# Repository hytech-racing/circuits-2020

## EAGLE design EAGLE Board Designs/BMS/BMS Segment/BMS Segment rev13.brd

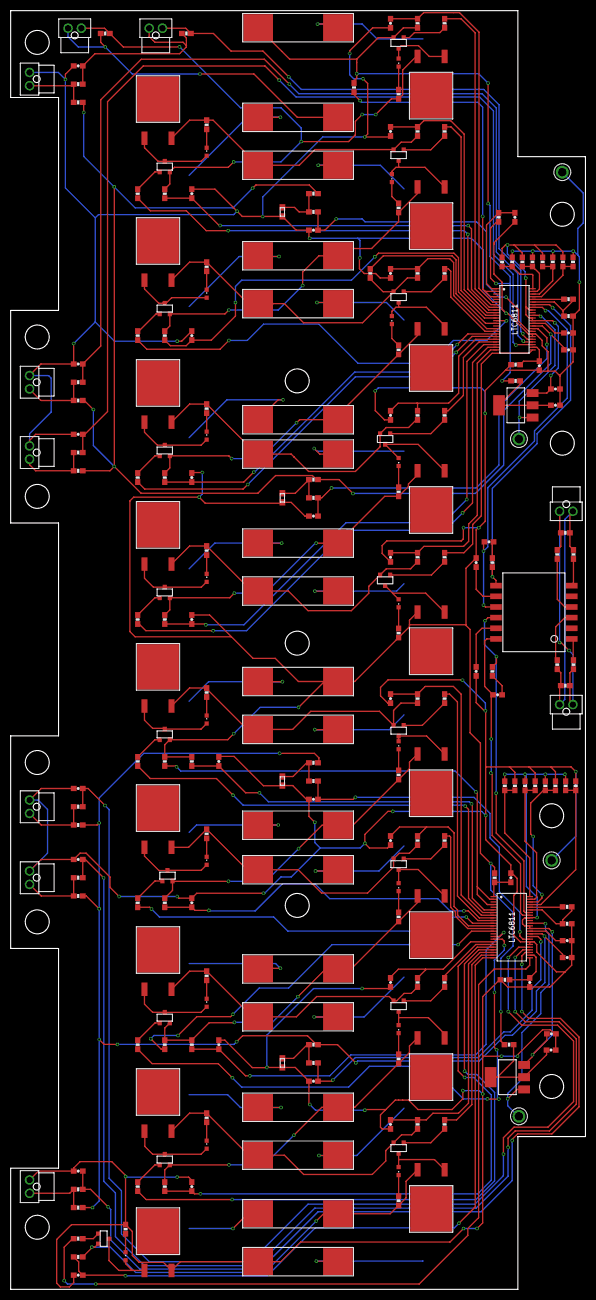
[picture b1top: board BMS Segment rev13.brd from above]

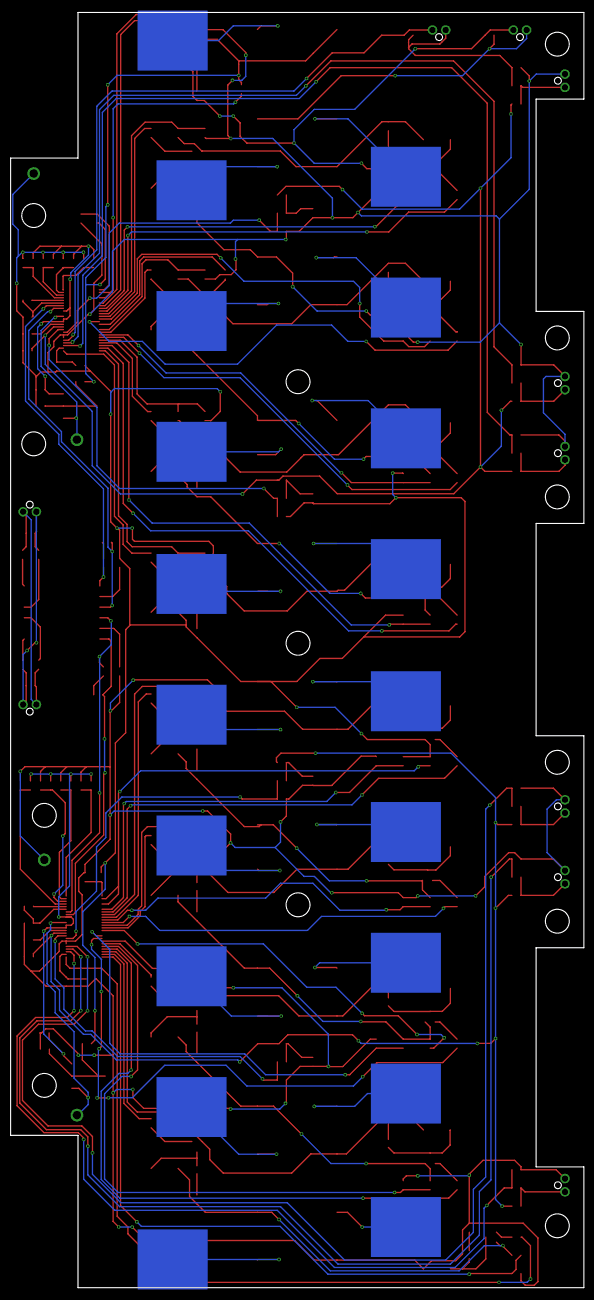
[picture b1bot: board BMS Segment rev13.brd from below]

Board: 2 copper layers, 108.0 x 240.3 mm, 286 parts (19 on the bottom side), 194 nets.

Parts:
AMS_CELL_TEST: AMS_CELL_TEST; NANO-FIT_VERTICAL-2
AMS_THERM_TEST: AMS_THERM_TEST; NANO-FIT_VERTICAL-2
C1_A, C1_B, C2_A, C2_B, C8_A, C8_B: 1uF; 0603-CAP
C3_A, C3_B: 15pF; 0603-CAP
C4_A, C4_B, C5_A: 10nF; 0603-CAP
C6_A, C6_B, C7_A, C7_B: 100nF; 0603-CAP
CELL0, CELL1, CELL2, CELL3, CELL4, CELL5, CELL6, CELL7, CELL8, CELL9, CELL10, CELL11, CELL12, CELL13, CELL14, CELL15, CELL16, CELL17, CELL18: BATTERY_SPRING_KEYSTONE5222; KEYSTONE5222
C_5: 10nF; 0603-CAP
DRAIN1:C, DRAIN2:C, DRAIN3:C, DRAIN4:C, DRAIN5:C, DRAIN6:C, DRAIN7:C, DRAIN8:C, DRAIN9:C, DRAIN10:C, DRAIN11:C, DRAIN12:C, DRAIN13:C, DRAIN14:C, DRAIN15:C, DRAIN16:C, DRAIN17:C, DRAIN18:C: 10nF; 0603-CAP
DRAIN1:DISCHARGE, DRAIN2:DISCHARGE, DRAIN3:DISCHARGE, DRAIN4:DISCHARGE, DRAIN5:DISCHARGE, DRAIN6:DISCHARGE, DRAIN7:DISCHARGE, DRAIN8:DISCHARGE, DRAIN9:DISCHARGE, DRAIN10:DISCHARGE, DRAIN11:DISCHARGE, DRAIN12:DISCHARGE, DRAIN13:DISCHARGE, DRAIN14:DISCHARGE, DRAIN15:DISCHARGE, DRAIN16:DISCHARGE, DRAIN17:DISCHARGE, DRAIN18:DISCHARGE: 5R; PWR163
DRAIN1:GATE, DRAIN2:GATE, DRAIN3:GATE, DRAIN4:GATE, DRAIN5:GATE, DRAIN6:GATE, DRAIN7:GATE, DRAIN8:GATE, DRAIN9:GATE, DRAIN10:GATE, DRAIN11:GATE, DRAIN12:GATE, DRAIN13:GATE, DRAIN14:GATE, DRAIN15:GATE, DRAIN16:GATE, DRAIN17:GATE, DRAIN18:GATE: 3K3; 0603-RES
DRAIN1:LED1, DRAIN2:LED1, DRAIN3:LED1, DRAIN4:LED1, DRAIN5:LED1, DRAIN6:LED1, DRAIN7:LED1, DRAIN8:LED1, DRAIN9:LED1, DRAIN10:LED1, DRAIN11:LED1, DRAIN12:LED1, DRAIN13:LED1, DRAIN14:LED1, DRAIN15:LED1, DRAIN16:LED1, DRAIN17:LED1, DRAIN18:LED1: RED; LED-603
DRAIN1:PFET, DRAIN2:PFET, DRAIN3:PFET, DRAIN4:PFET, DRAIN5:PFET, DRAIN6:PFET, DRAIN7:PFET, DRAIN8:PFET, DRAIN9:PFET, DRAIN10:PFET, DRAIN11:PFET, DRAIN12:PFET, DRAIN13:PFET, DRAIN14:PFET, DRAIN15:PFET, DRAIN16:PFET, DRAIN17:PFET, DRAIN18:PFET: P-CHANNEL_MOSFET_DMP3099L-7; SOT23
DRAIN1:R, DRAIN2:R, DRAIN3:R, DRAIN4:R, DRAIN5:R, DRAIN6:R, DRAIN7:R, DRAIN8:R, DRAIN9:R, DRAIN10:R, DRAIN11:R, DRAIN12:R, DRAIN13:R, DRAIN14:R, DRAIN15:R, DRAIN16:R, DRAIN17:R, DRAIN18:R: 100R; 0603-RES
DRAIN1:R1, DRAIN2:R1, DRAIN3:R1, DRAIN4:R1, DRAIN5:R1, DRAIN6:R1, DRAIN7:R1, DRAIN8:R1, DRAIN9:R1, DRAIN10:R1, DRAIN11:R1, DRAIN12:R1, DRAIN13:R1, DRAIN14:R1, DRAIN15:R1, DRAIN16:R1, DRAIN17:R1, DRAIN18:R1: 806R; 0603-RES
F0, F1, F2, F3, F4, F5, F6, F7, F8, F9, F10, F11, F12, F13, F14, F15, F16, F17, F18: 0001.2704.11; 5X20MM_FUSE
ISOSPI_A: ISOSPI; NANO-FIT_VERTICAL-2
ISOSPI_B: ISOSPI; NANO-FIT_VERTICAL-2
J1_A, J1_B, J2_A, J2_B, J3_A, J3_B, J4_A, J4_B, J5_A, J5_B, J6_A, J6_B, J7_A, J7_B, J8_A, J8_B: 0R; 0603-RES
J_CELL_A: 0R; 0603-RES
J_THERM_A: 0R; 0603-RES
Q1, Q2: NSV1C201MZ4; SOT223
R1_A, R1_B, R2_A, R2_B: 100R; 0603-RES
R3_A, R3_B: 402R; 0603-RES
R4_A, R4_B, R5_A, R5_B: 22R; 0603-RES
RB1_A, RB1_B: 1K2; 0603-RES
RB2_A, RB2_B: 806R; 0603-RES
RIN_A: 100R; 0603-RES
RIN_B: 100R; 0603-RES
RM_A: 100R; 0603-RES
RM_B: 100R; 0603-RES
RU1_A, RU1_B, RU2_A, RU2_B: 100R; 0603-RES
THERM1, THERM2, THERM3, THERM4: 10K; 0603
THERM1_A, THERM1_B, THERM2_A, THERM2_B, THERM3_A, THERM3_B: THERMISTOR; NANO-FIT_VERTICAL-2
THERM_FILTER1:C, THERM_FILTER2:C, THERM_FILTER3:C, THERM_FILTER4:C, THERM_FILTER5:C, THERM_FILTER6:C, THERM_FILTER7:C, THERM_FILTER8:C, THERM_FILTER9:C, THERM_FILTER10:C: 10nF; 0603-CAP
THERM_FILTER1:R, THERM_FILTER2:R, THERM_FILTER3:R, THERM_FILTER4:R, THERM_FILTER5:R, THERM_FILTER6:R, THERM_FILTER7:R, THERM_FILTER8:R, THERM_FILTER9:R, THERM_FILTER10:R: 100R; 0603-RES
THERM_FILTER1:R1, THERM_FILTER2:R1, THERM_FILTER3:R1, THERM_FILTER4:R1, THERM_FILTER5:R1, THERM_FILTER6:R1, THERM_FILTER7:R1, THERM_FILTER8:R1, THERM_FILTER9:R1, THERM_FILTER10:R1: 10K; 0603-RES
TRANSFORMER: HM2102NLT
U1, U2: LTC6811-2; LTC6811
U$5, U$6, U$7, U$8: TEST_POINT
U$9, U$10, U$11, U$12, U$13, U$14, U$15, U$16, U$17, U$18, U$19, U$26, U$27: M4_MOUNTING

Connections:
C0_A: C5_A.1, R2_A.2, U1.26
C0_B: C_5.1, R2_B.2, U2.26
C1_A: DRAIN10:C.1, DRAIN10:R.2, U1.24
C1_B: DRAIN1:C.1, DRAIN1:R.2, U2.24
C2_A: DRAIN11:C.1, DRAIN11:R.2, U1.22
C2_B: DRAIN2:C.1, DRAIN2:R.2, U2.22
C3_A: DRAIN12:C.1, DRAIN12:R.2, U1.20
C3_B: DRAIN3:C.1, DRAIN3:R.2, U2.20
C4_A: DRAIN13:C.1, DRAIN13:R.2, U1.18
C4_B: DRAIN4:C.1, DRAIN4:R.2, U2.18
C5_A: DRAIN14:C.1, DRAIN14:R.2, U1.16
C5_B: DRAIN5:C.1, DRAIN5:R.2, U2.16
C7_A: DRAIN15:C.1, DRAIN15:R.2, U1.12
C7_B: DRAIN6:C.1, DRAIN6:R.2, U2.12
C8_A: DRAIN16:C.1, DRAIN16:R.2, U1.10
C8_B: DRAIN7:C.1, DRAIN7:R.2, U2.10
C9_A: DRAIN17:C.1, DRAIN17:R.2, U1.8
C9_B: DRAIN8:C.1, DRAIN8:R.2, U2.8
C10_A: DRAIN18:C.1, DRAIN18:R.2, U1.6
C10_B: DRAIN9:C.1, DRAIN9:R.2, U2.6
CC0: CELL0.P$1, F0.P$1
CC1: CELL1.P$1, F1.P$1
CC2: CELL2.P$1, F2.P$1
CC3: CELL3.P$1, F3.P$1
CC4: CELL4.P$1, F4.P$1
CC5: CELL5.P$1, F5.P$1
CC6: CELL6.P$1, F6.P$1
CC7: CELL7.P$1, F7.P$1
CC8: CELL8.P$1, F8.P$1
CC9: CELL9.P$1, F9.P$1
CC10: CELL10.P$1, F10.P$1
CC11: CELL11.P$1, F11.P$1
CC12: CELL12.P$1, F12.P$1
CC13: CELL13.P$1, F13.P$1
CC14: CELL14.P$1, F14.P$1
CC15: CELL15.P$1, F15.P$1
CC16: CELL16.P$1, F16.P$1
CC17: CELL17.P$1, F17.P$1
CC18: CELL18.P$1, F18.P$1
DRAIN1:GATE: DRAIN1:GATE.1, DRAIN1:PFET.1
DRAIN1:N$1: DRAIN1:DISCHARGE.1, DRAIN1:LED1.A, DRAIN1:PFET.3
DRAIN1:N$2: DRAIN1:LED1.C, DRAIN1:R1.2
DRAIN2:GATE: DRAIN2:GATE.1, DRAIN2:PFET.1
DRAIN2:N$1: DRAIN2:DISCHARGE.1, DRAIN2:LED1.A, DRAIN2:PFET.3
DRAIN2:N$2: DRAIN2:LED1.C, DRAIN2:R1.2
DRAIN3:GATE: DRAIN3:GATE.1, DRAIN3:PFET.1
DRAIN3:N$1: DRAIN3:DISCHARGE.1, DRAIN3:LED1.A, DRAIN3:PFET.3
DRAIN3:N$2: DRAIN3:LED1.C, DRAIN3:R1.2
DRAIN4:GATE: DRAIN4:GATE.1, DRAIN4:PFET.1
DRAIN4:N$1: DRAIN4:DISCHARGE.1, DRAIN4:LED1.A, DRAIN4:PFET.3
DRAIN4:N$2: DRAIN4:LED1.C, DRAIN4:R1.2
DRAIN5:GATE: DRAIN5:GATE.1, DRAIN5:PFET.1
DRAIN5:N$1: DRAIN5:DISCHARGE.1, DRAIN5:LED1.A, DRAIN5:PFET.3
DRAIN5:N$2: DRAIN5:LED1.C, DRAIN5:R1.2
DRAIN6:GATE: DRAIN6:GATE.1, DRAIN6:PFET.1
DRAIN6:N$1: DRAIN6:DISCHARGE.1, DRAIN6:LED1.A, DRAIN6:PFET.3
DRAIN6:N$2: DRAIN6:LED1.C, DRAIN6:R1.2
DRAIN7:GATE: DRAIN7:GATE.1, DRAIN7:PFET.1
DRAIN7:N$1: DRAIN7:DISCHARGE.1, DRAIN7:LED1.A, DRAIN7:PFET.3
DRAIN7:N$2: DRAIN7:LED1.C, DRAIN7:R1.2
DRAIN8:GATE: DRAIN8:GATE.1, DRAIN8:PFET.1
DRAIN8:N$1: DRAIN8:DISCHARGE.1, DRAIN8:LED1.A, DRAIN8:PFET.3
DRAIN8:N$2: DRAIN8:LED1.C, DRAIN8:R1.2
DRAIN9:GATE: DRAIN9:GATE.1, DRAIN9:PFET.1
DRAIN9:N$1: DRAIN9:DISCHARGE.1, DRAIN9:LED1.A, DRAIN9:PFET.3
DRAIN9:N$2: DRAIN9:LED1.C, DRAIN9:R1.2
DRAIN10:GATE: DRAIN10:GATE.1, DRAIN10:PFET.1
DRAIN10:N$1: DRAIN10:DISCHARGE.1, DRAIN10:LED1.A, DRAIN10:PFET.3
DRAIN10:N$2: DRAIN10:LED1.C, DRAIN10:R1.2
DRAIN11:GATE: DRAIN11:GATE.1, DRAIN11:PFET.1
DRAIN11:N$1: DRAIN11:DISCHARGE.1, DRAIN11:LED1.A, DRAIN11:PFET.3
DRAIN11:N$2: DRAIN11:LED1.C, DRAIN11:R1.2
DRAIN12:GATE: DRAIN12:GATE.1, DRAIN12:PFET.1
DRAIN12:N$1: DRAIN12:DISCHARGE.1, DRAIN12:LED1.A, DRAIN12:PFET.3
DRAIN12:N$2: DRAIN12:LED1.C, DRAIN12:R1.2
DRAIN13:GATE: DRAIN13:GATE.1, DRAIN13:PFET.1
DRAIN13:N$1: DRAIN13:DISCHARGE.1, DRAIN13:LED1.A, DRAIN13:PFET.3
DRAIN13:N$2: DRAIN13:LED1.C, DRAIN13:R1.2
DRAIN14:GATE: DRAIN14:GATE.1, DRAIN14:PFET.1
DRAIN14:N$1: DRAIN14:DISCHARGE.1, DRAIN14:LED1.A, DRAIN14:PFET.3
DRAIN14:N$2: DRAIN14:LED1.C, DRAIN14:R1.2
DRAIN15:GATE: DRAIN15:GATE.1, DRAIN15:PFET.1
DRAIN15:N$1: DRAIN15:DISCHARGE.1, DRAIN15:LED1.A, DRAIN15:PFET.3
DRAIN15:N$2: DRAIN15:LED1.C, DRAIN15:R1.2
DRAIN16:GATE: DRAIN16:GATE.1, DRAIN16:PFET.1
DRAIN16:N$1: DRAIN16:DISCHARGE.1, DRAIN16:LED1.A, DRAIN16:PFET.3
DRAIN16:N$2: DRAIN16:LED1.C, DRAIN16:R1.2
DRAIN17:GATE: DRAIN17:GATE.1, DRAIN17:PFET.1
DRAIN17:N$1: DRAIN17:DISCHARGE.1, DRAIN17:LED1.A, DRAIN17:PFET.3
DRAIN17:N$2: DRAIN17:LED1.C, DRAIN17:R1.2
DRAIN18:GATE: DRAIN18:GATE.1, DRAIN18:PFET.1
DRAIN18:N$1: DRAIN18:DISCHARGE.1, DRAIN18:LED1.A, DRAIN18:PFET.3
DRAIN18:N$2: DRAIN18:LED1.C, DRAIN18:R1.2
DRIVE_A: Q1.1, U1.38, U$8.P$1
DRIVE_B: Q2.1, U2.38, U$7.P$1
GPIO1_A: THERM_FILTER6:C.1, THERM_FILTER6:R.1, U1.27
GPIO1_B: THERM_FILTER1:C.1, THERM_FILTER1:R.1, U2.27
GPIO2_A: THERM_FILTER7:C.1, THERM_FILTER7:R.1, U1.28
GPIO2_B: THERM_FILTER2:C.1, THERM_FILTER2:R.1, U2.28
GPIO3_A_POST: AMS_THERM_TEST.P$2, J_THERM_A.1, U1.29
GPIO3_A_PRE: AMS_THERM_TEST.P$1, J_THERM_A.2, THERM_FILTER8:C.1, THERM_FILTER8:R.1
GPIO3_B: THERM_FILTER3:C.1, THERM_FILTER3:R.1, U2.29
GPIO4_A: THERM_FILTER9:C.1, THERM_FILTER9:R.1, U1.32
GPIO4_B: THERM_FILTER4:C.1, THERM_FILTER4:R.1, U2.32
GPIO5_A: THERM_FILTER10:C.1, THERM_FILTER10:R.1, U1.33
GPIO5_B: THERM_FILTER5:C.1, THERM_FILTER5:R.1, U2.33
IM_A: C3_A.2, TRANSFORMER.P$9, U1.41
IM_B: C3_B.2, TRANSFORMER.P$12, U2.41
IP_A: R3_A.1, TRANSFORMER.P$7, U1.42
IP_B: R3_B.1, TRANSFORMER.P$10, U2.42
ISOSPI-M: ISOSPI_A.P$2, ISOSPI_B.P$2, R5_A.2, R5_B.2, RM_A.2, RM_B.2
ISOSPI-P: ISOSPI_A.P$1, ISOSPI_B.P$1, R4_A.2, R4_B.2, RM_A.1, RM_B.1
unnamed: C4_B.1, TRANSFORMER.P$11
unnamed: RB1_B.2, U2.44
unnamed: THERM1_B.P$1, THERM_FILTER1:R.2, THERM_FILTER1:R1.2
unnamed: RB1_B.1, RB2_B.2, U2.43
unnamed: R4_B.1, TRANSFORMER.P$3
unnamed: RB1_A.2, U1.44
unnamed: R5_B.1, TRANSFORMER.P$1
unnamed: J7_B.1, J8_B.1, U2.48
unnamed: J5_B.1, J6_B.1, U2.47
unnamed: C3_B.1, R3_B.2
unnamed: J3_B.1, J4_B.1, U2.46
unnamed: J1_B.1, J2_B.1, U2.45
unnamed: THERM1.2, THERM_FILTER5:R.2, THERM_FILTER5:R1.2
unnamed: THERM2_B.P$1, THERM_FILTER2:R.2, THERM_FILTER2:R1.2
unnamed: THERM2.2, THERM_FILTER4:R.2, THERM_FILTER4:R1.2
unnamed: RB1_A.1, RB2_A.2, U1.43
unnamed: C4_A.1, TRANSFORMER.P$8
unnamed: R4_A.1, TRANSFORMER.P$6
unnamed: R5_A.1, TRANSFORMER.P$4
unnamed: C3_A.1, R3_A.2
unnamed: THERM3_B.P$1, THERM_FILTER3:R.2, THERM_FILTER3:R1.2
unnamed: J7_A.1, J8_A.1, U1.48
unnamed: J5_A.1, J6_A.1, U1.47
unnamed: J3_A.1, J4_A.1, U1.46
unnamed: J1_A.1, J2_A.1, U1.45
unnamed: THERM4.2, THERM_FILTER9:R.2, THERM_FILTER9:R1.2
unnamed: THERM3_A.P$1, THERM_FILTER8:R.2, THERM_FILTER8:R1.2
unnamed: THERM3.2, THERM_FILTER10:R.2, THERM_FILTER10:R1.2
unnamed: THERM2_A.P$1, THERM_FILTER7:R.2, THERM_FILTER7:R1.2
unnamed: THERM1_A.P$1, THERM_FILTER6:R.2, THERM_FILTER6:R1.2
S1_A: DRAIN10:GATE.2, U1.25
S1_B: DRAIN1:GATE.2, U2.25
S2_A: DRAIN11:GATE.2, U1.23
S2_B: DRAIN2:GATE.2, U2.23
S3_A: DRAIN12:GATE.2, U1.21
S3_B: DRAIN3:GATE.2, U2.21
S4_A: DRAIN13:GATE.2, U1.19
S4_B: DRAIN4:GATE.2, U2.19
S5_A: DRAIN14:GATE.2, U1.17
S5_B: DRAIN5:GATE.2, U2.17
S7_A: DRAIN15:GATE.2, U1.13
S7_B: DRAIN6:GATE.2, U2.13
S8_A: DRAIN16:GATE.2, U1.11
S8_B: DRAIN7:GATE.2, U2.11
S9_A: DRAIN17:GATE.2, U1.9
S9_B: DRAIN8:GATE.2, U2.9
S10_A: DRAIN18:GATE.2, U1.7
S10_B: DRAIN9:GATE.2, U2.7
SENSE1: DRAIN1:PFET.2, DRAIN1:R.1, DRAIN2:DISCHARGE.2, DRAIN2:R1.1, F1.P$2
SENSE2: DRAIN2:PFET.2, DRAIN2:R.1, DRAIN3:DISCHARGE.2, DRAIN3:R1.1, F2.P$2
SENSE3: DRAIN3:PFET.2, DRAIN3:R.1, DRAIN4:DISCHARGE.2, DRAIN4:R1.1, F3.P$2
SENSE4: DRAIN4:PFET.2, DRAIN4:R.1, DRAIN5:DISCHARGE.2, DRAIN5:R1.1, F4.P$2
SENSE5: DRAIN5:PFET.2, DRAIN5:R.1, DRAIN6:DISCHARGE.2, DRAIN6:R1.1, F5.P$2, RU2_B.1
SENSE6: DRAIN6:PFET.2, DRAIN6:R.1, DRAIN7:DISCHARGE.2, DRAIN7:R1.1, F6.P$2
SENSE7: DRAIN7:PFET.2, DRAIN7:R.1, DRAIN8:DISCHARGE.2, DRAIN8:R1.1, F7.P$2
SENSE8: DRAIN8:PFET.2, DRAIN8:R.1, DRAIN9:DISCHARGE.2, DRAIN9:R1.1, F8.P$2
SENSE10: DRAIN10:PFET.2, DRAIN10:R.1, DRAIN11:DISCHARGE.2, DRAIN11:R1.1, F10.P$2
SENSE11: DRAIN11:PFET.2, DRAIN11:R.1, DRAIN12:DISCHARGE.2, DRAIN12:R1.1, F11.P$2
SENSE12: DRAIN12:PFET.2, DRAIN12:R.1, DRAIN13:DISCHARGE.2, DRAIN13:R1.1, F12.P$2
SENSE13: DRAIN13:PFET.2, DRAIN13:R.1, DRAIN14:DISCHARGE.2, DRAIN14:R1.1, F13.P$2
SENSE14: DRAIN14:PFET.2, DRAIN14:R.1, DRAIN15:DISCHARGE.2, DRAIN15:R1.1, F14.P$2, RU2_A.1
SENSE15: DRAIN15:PFET.2, DRAIN15:R.1, DRAIN16:DISCHARGE.2, DRAIN16:R1.1, F15.P$2
SENSE16: DRAIN16:PFET.2, DRAIN16:R.1, DRAIN17:DISCHARGE.2, DRAIN17:R1.1, F16.P$2
SENSE17_POST: AMS_CELL_TEST.P$2, DRAIN17:PFET.2, DRAIN17:R.1, DRAIN18:DISCHARGE.2, DRAIN18:R1.1, J_CELL_A.2
SENSE17_PRE: AMS_CELL_TEST.P$1, F17.P$2, J_CELL_A.1
SENSE18: DRAIN18:PFET.2, DRAIN18:R.1, F18.P$2, R1_A.1, RIN_A.1, RU1_A.1
UNUSED1_A: RU1_A.2, U1.2, U1.4
UNUSED1_B: RU1_B.2, U2.2, U2.4
UNUSED2_A: RU2_A.2, U1.14
UNUSED2_B: RU2_B.2, U2.14
V+_A: C6_A.1, R1_A.2, U1.1
V+_B: C6_B.1, R1_B.2, U2.1
V-_A: C1_A.2, C2_A.2, C4_A.2, C5_A.2, C6_A.2, C7_A.2, C8_A.2, DRAIN9:PFET.2, DRAIN9:R.1, DRAIN10:C.2, DRAIN10:DISCHARGE.2, DRAIN10:R1.1, DRAIN11:C.2, DRAIN12:C.2, DRAIN13:C.2, DRAIN14:C.2, DRAIN15:C.2, DRAIN16:C.2, DRAIN17:C.2, DRAIN18:C.2, F9.P$2, J1_A.2, J3_A.2, J5_A.2, J7_A.2, R1_B.1, R2_A.1, RB2_A.1, RIN_B.1, RU1_B.1, THERM1_A.P$2, THERM2_A.P$2, THERM3.1, THERM3_A.P$2, THERM4.1, THERM_FILTER6:C.2, THERM_FILTER7:C.2, THERM_FILTER8:C.2, THERM_FILTER9:C.2, THERM_FILTER10:C.2, U1.30, U1.31, U$5.P$1
V-_B: C1_B.2, C2_B.2, C4_B.2, C6_B.2, C7_B.2, C8_B.2, C_5.2, DRAIN1:C.2, DRAIN1:DISCHARGE.2, DRAIN1:R1.1, DRAIN2:C.2, DRAIN3:C.2, DRAIN4:C.2, DRAIN5:C.2, DRAIN6:C.2, DRAIN7:C.2, DRAIN8:C.2, DRAIN9:C.2, F0.P$2, J1_B.2, J3_B.2, J5_B.2, J7_B.2, R2_B.1, RB2_B.1, THERM1.1, THERM1_B.P$2, THERM2.1, THERM2_B.P$2, THERM3_B.P$2, THERM_FILTER1:C.2, THERM_FILTER2:C.2, THERM_FILTER3:C.2, THERM_FILTER4:C.2, THERM_FILTER5:C.2, U2.30, U2.31, U$6.P$1
VIN_A: C7_A.1, Q1.2, Q1.4, RIN_A.2
VIN_B: C7_B.1, Q2.2, Q2.4, RIN_B.2
VREF1_A: C2_A.1, U1.35
VREF1_B: C2_B.1, U2.35
VREF2_A: C1_A.1, THERM_FILTER6:R1.1, THERM_FILTER7:R1.1, THERM_FILTER8:R1.1, THERM_FILTER9:R1.1, THERM_FILTER10:R1.1, U1.34
VREF2_B: C1_B.1, THERM_FILTER1:R1.1, THERM_FILTER2:R1.1, THERM_FILTER3:R1.1, THERM_FILTER4:R1.1, THERM_FILTER5:R1.1, U2.34
VREG_A: C8_A.1, J2_A.2, J4_A.2, J6_A.2, J8_A.2, Q1.3, U1.36, U1.37, U1.40
VREG_B: C8_B.1, J2_B.2, J4_B.2, J6_B.2, J8_B.2, Q2.3, U2.36, U2.37, U2.40

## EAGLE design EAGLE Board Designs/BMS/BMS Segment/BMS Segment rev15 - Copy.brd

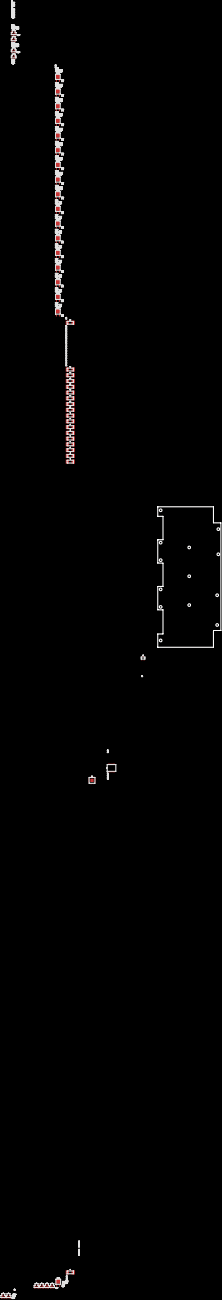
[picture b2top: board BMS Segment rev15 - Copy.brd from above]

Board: 2 copper layers, 108.0 x 240.3 mm, 239 parts (0 on the bottom side), 169 nets, no tracks yet.

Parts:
C1, C2, C3, C4, C5, C6, C7, C8, C9, C10: 0603-CAP
CELL1:C1, CELL2:C1, CELL3:C1, CELL4:C1, CELL5:C1, CELL6:C1, CELL7:C1, CELL8:C1, CELL9:C1, CELL10:C1, CELL11:C1, CELL12:C1, CELL13:C1, CELL14:C1, CELL15:C1, CELL16:C1, CELL17:C1, CELL18:C1: 0603-CAP
CELL1:D1, CELL2:D1, CELL3:D1, CELL4:D1, CELL5:D1, CELL6:D1, CELL7:D1, CELL8:D1, CELL9:D1, CELL10:D1, CELL11:D1, CELL12:D1, CELL13:D1, CELL14:D1, CELL15:D1, CELL16:D1, CELL17:D1, CELL18:D1: 0603-LED
CELL1:Q1, CELL2:Q1, CELL3:Q1, CELL4:Q1, CELL5:Q1, CELL6:Q1, CELL7:Q1, CELL8:Q1, CELL9:Q1, CELL10:Q1, CELL11:Q1, CELL12:Q1, CELL13:Q1, CELL14:Q1, CELL15:Q1, CELL16:Q1, CELL17:Q1, CELL18:Q1: TRANSISTOR_P_MOS_SOT23_SI2369DS-T1-GE3; SOT-23
CELL1:R1, CELL2:R1, CELL3:R1, CELL4:R1, CELL5:R1, CELL6:R1, CELL7:R1, CELL8:R1, CELL9:R1, CELL10:R1, CELL11:R1, CELL12:R1, CELL13:R1, CELL14:R1, CELL15:R1, CELL16:R1, CELL17:R1, CELL18:R1: RESISTOR_0603_100; 0603-RES
CELL1:R2, CELL2:R2, CELL3:R2, CELL4:R2, CELL5:R2, CELL6:R2, CELL7:R2, CELL8:R2, CELL9:R2, CELL10:R2, CELL11:R2, CELL12:R2, CELL13:R2, CELL14:R2, CELL15:R2, CELL16:R2, CELL17:R2, CELL18:R2: RESISTOR_0603_3.3K; 0603-RES
CELL1:R3, CELL2:R3, CELL3:R3, CELL4:R3, CELL5:R3, CELL6:R3, CELL7:R3, CELL8:R3, CELL9:R3, CELL10:R3, CELL11:R3, CELL12:R3, CELL13:R3, CELL14:R3, CELL15:R3, CELL16:R3, CELL17:R3, CELL18:R3: RESISTOR_PWR163_5; PWR163
CELL1:R4, CELL2:R4, CELL3:R4, CELL4:R4, CELL5:R4, CELL6:R4, CELL7:R4, CELL8:R4, CELL9:R4, CELL10:R4, CELL11:R4, CELL12:R4, CELL13:R4, CELL14:R4, CELL15:R4, CELL16:R4, CELL17:R4, CELL18:R4: RESISTOR_0603_1K; 0603-RES
F0, F1, F2, F3, F4, F5, F6, F7, F8, F9, F10, F11, F12, F13, F14, F15, F16, F17, F18: 0885
J0, J1, J2, J3, J4, J5, J6, J7, J8, J9, J10, J11, J12, J13, J14, J15, J16, J17, J18: CONNECTOR-1; 807-22-001-10-02X101
J19, J20, J21, J22, J23, J24, J25, J26, J27, J28: MOLEX_NANOFIT_SMD_VERTICAL_02
Q3: SOT223
R1, R3, R7: RESISTOR_0603_100; 0603-RES
R2, R4, R5, R6: RESISTOR_0603_60.4; 0603-RES
R8, R9: RESISTOR_0603_1K; 0603-RES
RT1, RT2, RT3: THERMISTOR; 0603-RES
T1: TRANSFORMERHM2102NLT; HM2102NLT
THERM1:C1, THERM2:C1, THERM3:C1, THERM4:C1, THERM5:C1, THERM6:C1, THERM7:C1, THERM8:C1, THERM9:C1: 0603-CAP
THERM1:R1, THERM2:R1, THERM3:R1, THERM4:R1, THERM5:R1, THERM6:R1, THERM7:R1, THERM8:R1, THERM9:R1: RESISTOR_0603_100; 0603-RES
THERM1:R2, THERM2:R2, THERM3:R2, THERM4:R2, THERM5:R2, THERM6:R2, THERM7:R2, THERM8:R2, THERM9:R2: RESISTOR_0603_10K; 0603-RES
U1: LTC6813; LQFP-64
U$9, U$10, U$11, U$12, U$13, U$14, U$15, U$16, U$17, U$18, U$19, U$26, U$27: M4_MOUNTING

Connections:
C0: C10.1, R7.2, U1.38
C1: CELL1:C1.1, CELL1:R1.2, U1.36
C2: CELL2:C1.1, CELL2:R1.2, U1.34
C3: CELL3:C1.1, CELL3:R1.2, U1.32
C4: CELL4:C1.1, CELL4:R1.2, U1.30
C5: CELL5:C1.1, CELL5:R1.2, U1.28
C6: CELL6:C1.1, CELL6:R1.2, U1.26
C7: CELL7:C1.1, CELL7:R1.2, U1.24
C8: CELL8:C1.1, CELL8:R1.2, U1.22
C9: CELL9:C1.1, CELL9:R1.2, U1.20
C10: CELL10:C1.1, CELL10:R1.2, U1.18
C11: CELL11:C1.1, CELL11:R1.2, U1.16
C12: CELL12:C1.1, CELL12:R1.2, U1.14
C13: CELL13:C1.1, CELL13:R1.2, U1.12
C14: CELL14:C1.1, CELL14:R1.2, U1.10
C15: CELL15:C1.1, CELL15:R1.2, U1.8
C16: CELL16:C1.1, CELL16:R1.2, U1.6
C17: CELL17:C1.1, CELL17:R1.2, U1.4
C18: CELL18:C1.1, CELL18:R1.2, R1.2, R3.1, U1.2
CC0: F0.1, J0.1
CC1: F1.1, J1.1
CC2: F2.1, J2.1
CC3: F3.1, J3.1
CC4: F4.1, J4.1
CC5: F5.1, J5.1
CC6: F6.1, J6.1
CC7: F7.1, J7.1
CC8: F8.1, J8.1
CC9: F9.1, J9.1
CC10: F10.1, J10.1
CC11: F11.1, J11.1
CC12: F12.1, J12.1
CC13: F13.1, J13.1
CC14: F14.1, J14.1
CC15: F15.1, J15.1
CC16: F16.1, J16.1
CC17: F17.1, J17.1
CC18: F18.1, J18.1
CELL1:N$5: CELL1:Q1.1, CELL1:R2.1
CELL1:N$6: CELL1:D1.2, CELL1:Q1.3, CELL1:R3.2
CELL1:N$7: CELL1:D1.1, CELL1:R4.2
CELL2:N$5: CELL2:Q1.1, CELL2:R2.1
CELL2:N$6: CELL2:D1.2, CELL2:Q1.3, CELL2:R3.2
CELL2:N$7: CELL2:D1.1, CELL2:R4.2
CELL3:N$5: CELL3:Q1.1, CELL3:R2.1
CELL3:N$6: CELL3:D1.2, CELL3:Q1.3, CELL3:R3.2
CELL3:N$7: CELL3:D1.1, CELL3:R4.2
CELL4:N$5: CELL4:Q1.1, CELL4:R2.1
CELL4:N$6: CELL4:D1.2, CELL4:Q1.3, CELL4:R3.2
CELL4:N$7: CELL4:D1.1, CELL4:R4.2
CELL5:N$5: CELL5:Q1.1, CELL5:R2.1
CELL5:N$6: CELL5:D1.2, CELL5:Q1.3, CELL5:R3.2
CELL5:N$7: CELL5:D1.1, CELL5:R4.2
CELL6:N$5: CELL6:Q1.1, CELL6:R2.1
CELL6:N$6: CELL6:D1.2, CELL6:Q1.3, CELL6:R3.2
CELL6:N$7: CELL6:D1.1, CELL6:R4.2
CELL7:N$5: CELL7:Q1.1, CELL7:R2.1
CELL7:N$6: CELL7:D1.2, CELL7:Q1.3, CELL7:R3.2
CELL7:N$7: CELL7:D1.1, CELL7:R4.2
CELL8:N$5: CELL8:Q1.1, CELL8:R2.1
CELL8:N$6: CELL8:D1.2, CELL8:Q1.3, CELL8:R3.2
CELL8:N$7: CELL8:D1.1, CELL8:R4.2
CELL9:N$5: CELL9:Q1.1, CELL9:R2.1
CELL9:N$6: CELL9:D1.2, CELL9:Q1.3, CELL9:R3.2
CELL9:N$7: CELL9:D1.1, CELL9:R4.2
CELL10:N$5: CELL10:Q1.1, CELL10:R2.1
CELL10:N$6: CELL10:D1.2, CELL10:Q1.3, CELL10:R3.2
CELL10:N$7: CELL10:D1.1, CELL10:R4.2
CELL11:N$5: CELL11:Q1.1, CELL11:R2.1
CELL11:N$6: CELL11:D1.2, CELL11:Q1.3, CELL11:R3.2
CELL11:N$7: CELL11:D1.1, CELL11:R4.2
CELL12:N$5: CELL12:Q1.1, CELL12:R2.1
CELL12:N$6: CELL12:D1.2, CELL12:Q1.3, CELL12:R3.2
CELL12:N$7: CELL12:D1.1, CELL12:R4.2
CELL13:N$5: CELL13:Q1.1, CELL13:R2.1
CELL13:N$6: CELL13:D1.2, CELL13:Q1.3, CELL13:R3.2
CELL13:N$7: CELL13:D1.1, CELL13:R4.2
CELL14:N$5: CELL14:Q1.1, CELL14:R2.1
CELL14:N$6: CELL14:D1.2, CELL14:Q1.3, CELL14:R3.2
CELL14:N$7: CELL14:D1.1, CELL14:R4.2
CELL15:N$5: CELL15:Q1.1, CELL15:R2.1
CELL15:N$6: CELL15:D1.2, CELL15:Q1.3, CELL15:R3.2
CELL15:N$7: CELL15:D1.1, CELL15:R4.2
CELL16:N$5: CELL16:Q1.1, CELL16:R2.1
CELL16:N$6: CELL16:D1.2, CELL16:Q1.3, CELL16:R3.2
CELL16:N$7: CELL16:D1.1, CELL16:R4.2
CELL17:N$5: CELL17:Q1.1, CELL17:R2.1
CELL17:N$6: CELL17:D1.2, CELL17:Q1.3, CELL17:R3.2
CELL17:N$7: CELL17:D1.1, CELL17:R4.2
CELL18:N$5: CELL18:Q1.1, CELL18:R2.1
CELL18:N$6: CELL18:D1.2, CELL18:Q1.3, CELL18:R3.2
CELL18:N$7: CELL18:D1.1, CELL18:R4.2
GPIO1: J28.1, U1.39
GPIO1_PRE: J28.2, THERM1:C1.1, THERM1:R1.1
GPIO2: THERM2:C1.1, THERM2:R1.1, U1.40
GPIO3: THERM3:C1.1, THERM3:R1.1, U1.41
GPIO4: THERM4:C1.1, THERM4:R1.1, U1.42
GPIO5: THERM5:C1.1, THERM5:R1.1, U1.43
GPIO6: THERM6:C1.1, THERM6:R1.1, U1.44
GPIO7: THERM7:C1.1, THERM7:R1.1, U1.45
GPIO8: THERM8:C1.1, THERM8:R1.1, U1.46
GPIO9: THERM9:C1.1, THERM9:R1.1, U1.47
IMA: R6.1, T1.9, U1.61
IMB: R2.1, T1.12, U1.63
IPA: R5.2, T1.7, U1.62
IPB: R4.2, T1.10, U1.64
ISO_IMA: J19.2, T1.4
ISO_IMB: J20.2, T1.1
ISO_IPA: J19.1, T1.6
ISO_IPB: J20.1, T1.3
unnamed: R8.1, R9.2, U1.58
unnamed: R8.2, U1.57
unnamed: C8.2, R5.1, R6.2
unnamed: C5.1, T1.11
unnamed: Q3.1, U1.49
unnamed: C3.1, Q3.3, U1.48, U1.52, U1.55
unnamed: C4.1, Q3.2, Q3.4, R1.1
unnamed: C7.1, T1.8
unnamed: C9.2, R2.2, R4.1
unnamed: C2.1, U1.51
S1: CELL1:R2.2, U1.37
S2: CELL2:R2.2, U1.35
S3: CELL3:R2.2, U1.33
S4: CELL4:R2.2, U1.31
S5: CELL5:R2.2, U1.29
S6: CELL6:R2.2, U1.27
S7: CELL7:R2.2, U1.25
S8: CELL8:R2.2, U1.23
S9: CELL9:R2.2, U1.21
S10: CELL10:R2.2, U1.19
S11: CELL11:R2.2, U1.17
S12: CELL12:R2.2, U1.15
S13: CELL13:R2.2, U1.13
S14: CELL14:R2.2, U1.11
S15: CELL15:R2.2, U1.9
S16: CELL16:R2.2, U1.7
S17: CELL17:R2.2, U1.5
S18: CELL18:R2.2, U1.3
SENSE1: CELL1:Q1.2, CELL1:R1.1, CELL2:R3.1, CELL2:R4.1, F1.2
SENSE2: CELL2:Q1.2, CELL2:R1.1, CELL3:R3.1, CELL3:R4.1, F2.2
SENSE3: CELL3:Q1.2, CELL3:R1.1, CELL4:R3.1, CELL4:R4.1, F3.2
SENSE4: CELL4:Q1.2, CELL4:R1.1, CELL5:R3.1, CELL5:R4.1, F4.2
SENSE5: CELL5:Q1.2, CELL5:R1.1, CELL6:R3.1, CELL6:R4.1, F5.2
SENSE6: CELL6:Q1.2, CELL6:R1.1, CELL7:R3.1, CELL7:R4.1, F6.2
SENSE7: CELL7:Q1.2, CELL7:R1.1, CELL8:R3.1, CELL8:R4.1, F7.2
SENSE8: CELL8:Q1.2, CELL8:R1.1, CELL9:R3.1, CELL9:R4.1, F8.2
SENSE9: CELL9:Q1.2, CELL9:R1.1, CELL10:R3.1, CELL10:R4.1, F9.2
SENSE10: CELL10:Q1.2, CELL10:R1.1, CELL11:R3.1, CELL11:R4.1, F10.2
SENSE11: CELL11:Q1.2, CELL11:R1.1, CELL12:R3.1, CELL12:R4.1, F11.2
SENSE12: CELL12:Q1.2, CELL12:R1.1, CELL13:R3.1, CELL13:R4.1, F12.2
SENSE13: CELL13:Q1.2, CELL13:R1.1, CELL14:R3.1, CELL14:R4.1, F13.2
SENSE14: CELL14:Q1.2, CELL14:R1.1, CELL15:R3.1, CELL15:R4.1, F14.2
SENSE15: CELL15:Q1.2, CELL15:R1.1, CELL16:R3.1, CELL16:R4.1, F15.2
SENSE16: CELL16:Q1.2, CELL16:R1.1, CELL17:R3.1, CELL17:R4.1, F16.2
SENSE17: CELL17:Q1.2, CELL17:R1.1, CELL18:R3.1, CELL18:R4.1, J27.2
SENSE17_PRE: F17.2, J27.1
SENSE18: CELL18:Q1.2, CELL18:R1.1, F18.2
THERM1: J21.1, THERM1:R1.2, THERM1:R2.1
THERM2: J22.1, THERM2:R1.2, THERM2:R2.1
THERM3: J23.1, THERM3:R1.2, THERM3:R2.1
THERM4: J24.1, THERM4:R1.2, THERM4:R2.1
THERM5: J25.1, THERM5:R1.2, THERM5:R2.1
THERM6: J26.1, THERM6:R1.2, THERM6:R2.1
THERM7: RT1.2, THERM7:R1.2, THERM7:R2.1
THERM8: RT2.2, THERM8:R1.2, THERM8:R2.1
THERM9: RT3.2, THERM9:R1.2, THERM9:R2.1
V+: C6.1, R3.2, U1.1
V-: C1.2, C2.2, C3.2, C4.2, C5.2, C6.2, C7.2, C8.1, C9.1, C10.2, CELL1:C1.2, CELL1:R3.1, CELL1:R4.1, CELL2:C1.2, CELL3:C1.2, CELL4:C1.2, CELL5:C1.2, CELL6:C1.2, CELL7:C1.2, CELL8:C1.2, CELL9:C1.2, CELL10:C1.2, CELL11:C1.2, CELL12:C1.2, CELL13:C1.2, CELL14:C1.2, CELL15:C1.2, CELL16:C1.2, CELL17:C1.2, CELL18:C1.2, F0.2, J21.2, J22.2, J23.2, J24.2, J25.2, J26.2, R7.1, R9.1, RT1.1, RT2.1, RT3.1, THERM1:C1.2, THERM2:C1.2, THERM3:C1.2, THERM4:C1.2, THERM5:C1.2, THERM6:C1.2, THERM7:C1.2, THERM8:C1.2, THERM9:C1.2, U1.59, U1.60, U1.65
VREF2: C1.1, THERM1:R2.2, THERM2:R2.2, THERM3:R2.2, THERM4:R2.2, THERM5:R2.2, THERM6:R2.2, THERM7:R2.2, THERM8:R2.2, THERM9:R2.2, U1.50

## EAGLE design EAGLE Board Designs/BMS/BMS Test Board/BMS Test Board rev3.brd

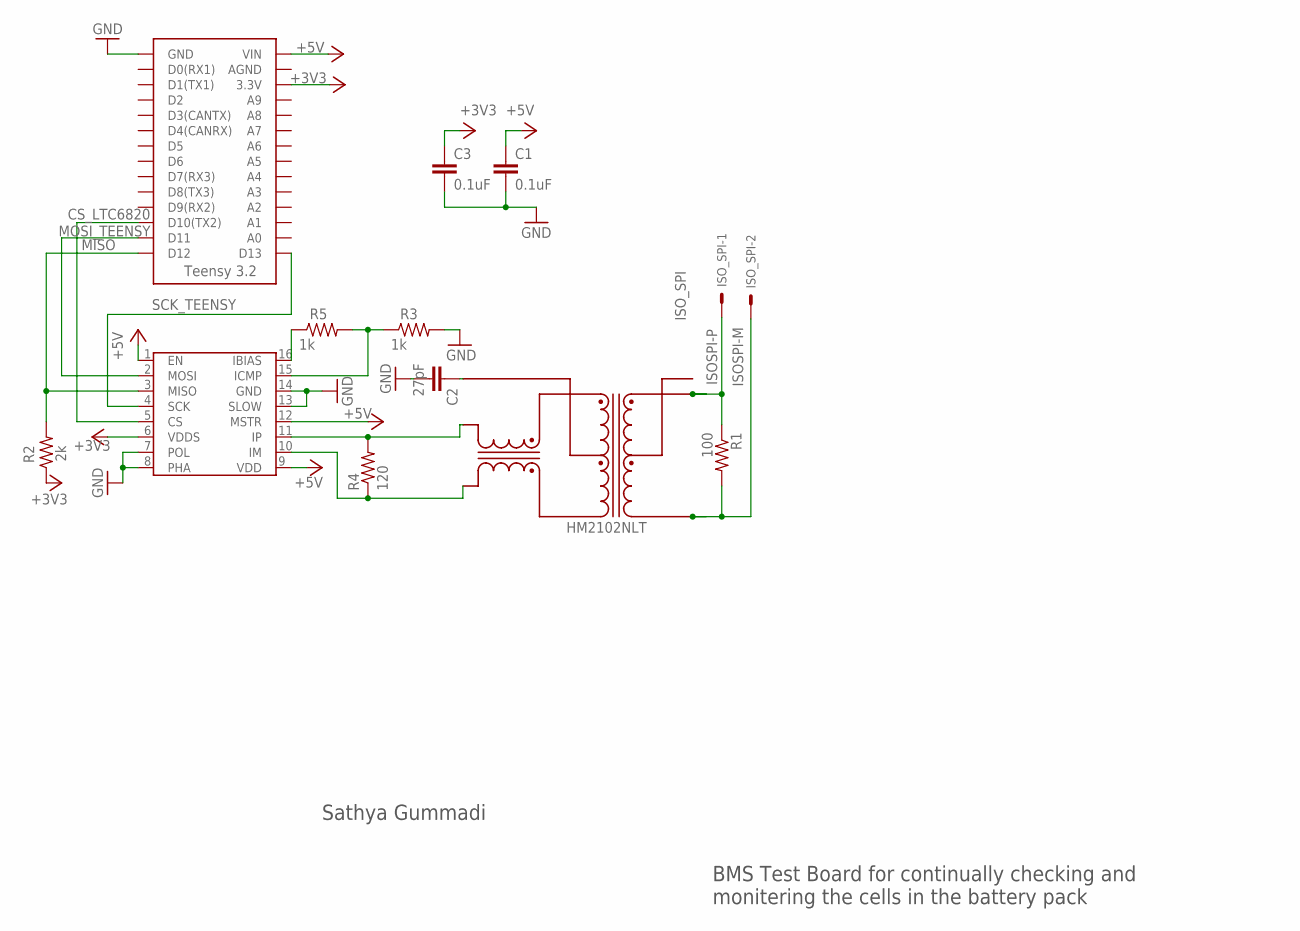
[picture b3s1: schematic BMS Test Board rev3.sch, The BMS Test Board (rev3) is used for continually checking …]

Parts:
C1, C3: 0.1uF; 0603-CAP
C2: 27pF; 0603-CAP
ISO_SPI: ISO_SPI; NANO-FIT_VERTICAL-2
R1: 100; 0603-RES
R2: 2k; 0603-RES
R3, R5: 1k; 0603-RES
R4: 120; 0603-RES
U$1: HM2102NLT
U$2: LTC6820; MSOP-16
U$3: TEENSY_3.2_SIMPLE

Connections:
+3V3: C3.2, R2.1, U$2.6 (VDDS), U$3.3.3V
+5V: C1.2, U$2.1 (EN), U$2.9 (VDD), U$2.12 (MSTR), U$3.VIN
CS_LTC6820: U$2.5 (CS), U$3.D10(TX2)
GND: C1.1, C2.2, C3.1, R3.2, U$2.7 (POL), U$2.8 (PHA), U$2.13 (SLOW), U$2.14 (GND), U$3.GND
IM: R4.1, U$1.P$10 (TD-), U$2.10 (IM)
IP: R4.2, U$1.P$12 (TD+), U$2.11 (IP)
ISOSPI-M: ISO_SPI.P$2, R1.2, U$1.P$3 (MX-)
ISOSPI-P: ISO_SPI.P$1, R1.1, U$1.P$1 (MX+)
MISO: R2.2, U$2.3 (MISO), U$3.D12
MOSI_TEENSY: U$2.2 (MOSI), U$3.D11
unnamed: C2.1, U$1.P$11 (TCT)
unnamed: R5.1, U$2.16 (IBIAS)
unnamed: R3.1, R5.2, U$2.15 (ICMP)
SCK_TEENSY: U$2.4 (SCK), U$3.D13

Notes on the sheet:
Sathya Gummadi
BMS Test Board for continually checking and monitering the cells in the battery pack

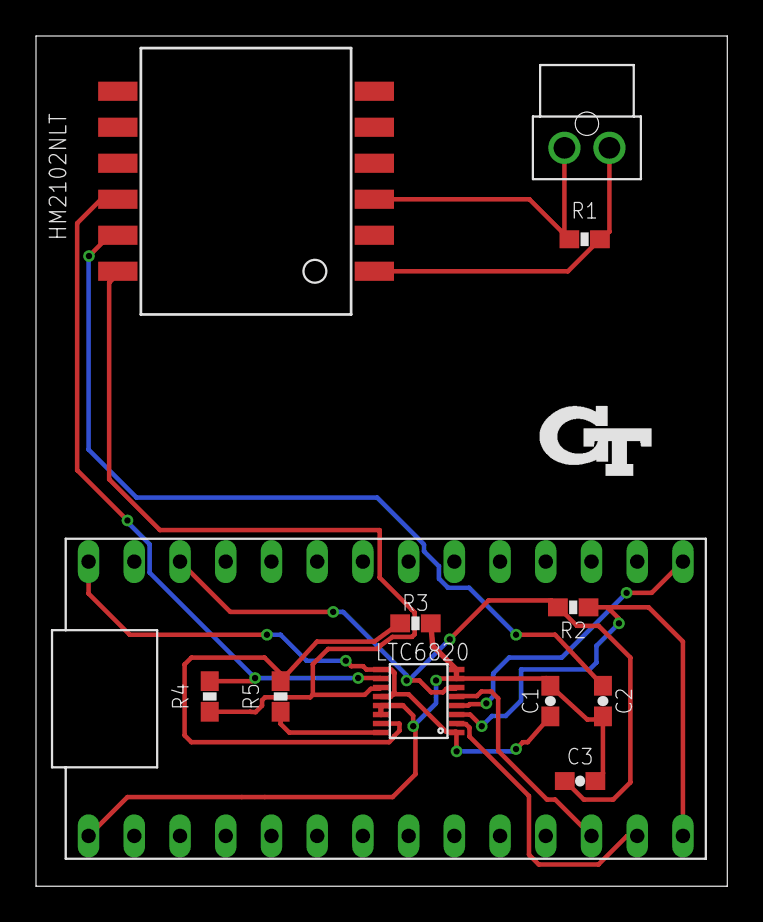
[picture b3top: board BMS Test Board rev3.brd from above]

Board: 2 copper layers, 38.4 x 47.2 mm, 12 parts (0 on the bottom side), 14 nets.
